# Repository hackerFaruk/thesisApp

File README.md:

# thesisApp

This app is made to work as part of my master thesis.
Controls motors & observes data of an exoskeleton.
Exoskeleton is also built as part of my master

Thesis name:
#  Development of Body Position and Muscle State Analyzing Personal Trainer Device with Mobile App Support

Thesis Ref no ( Turkey) : 10604256

my orcid 0000-0001-7512-0224

# Folder Structure 

control_app -> file you can find mobile app made with flutter  

Step Files ->  you can step files for either prodcution or editting  parts used in thesis   

Visuals -> you can find technical drawings of parts and also pictures of end product  

Embeded -> you can find files regarding embeded files   

Electronics -> you can find electronics for embeded system in here 

# Requirements  For  Flutter App 

Flutter SDK
Android Toolchain
Java Development Kit 

You can either visit flutter.dev for setup your development environment ( https://docs.flutter.dev/get-started/install )

or 

1- manually install flutter sdk   

2- run command <flutter doctor>  to check if any requirements are missing 

3- Get Java development kit ( JDK) from oracle

4- to get android tool chain use  Android Studio > Tools > SDK tools > Android SDK Command-line Tools >Apply to get sdk 

5- run <flutter doctor --android-licenses>  this step might require 

Recomended : Use Android Stuido to setup and device emulator (  this is not a requiremnt for this to work but definetly useful for development or testing )

# Versions List 

sdk: '>=2.19.4 <3.0.0' 

cupertino_icons: ^1.0.2

flutter_bluetooth_serial: ^0.4.0

flutter_lints: ^2.0.0

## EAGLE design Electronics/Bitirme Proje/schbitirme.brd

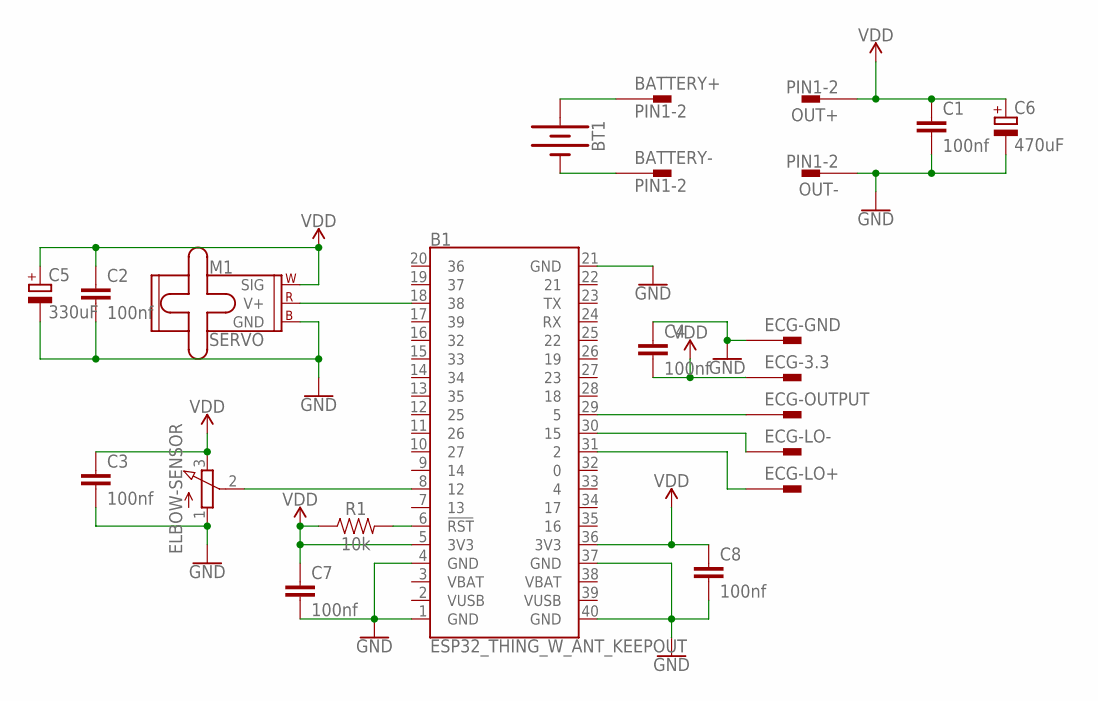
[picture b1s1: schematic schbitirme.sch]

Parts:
B1: ESP32_THING_W_ANT_KEEPOUT; ESP32_THING
BATTERY+: PIN1-2; 62221
BATTERY-: PIN1-2; 62221
BT1: BATTERY-18650; BATTERY_18650-HOLDER
C1, C2, C3, C4, C7, C8: 100nf; C2.5-3
C5: 330uF; PANASONIC_D
C6: 470uF; PANASONIC_D
ECG-3.3: PIN1-2; 62221
ECG-GND: PIN1-2; 62221
ECG-LO+: PIN1-2; 62221
ECG-LO-: PIN1-2; 62221
ECG-OUTPUT: PIN1-2; 62221
ELBOW-SENSOR: 3RP/1610N
M1: SERVO; 1X03
OUT+: PIN1-2; 62221
OUT-: PIN1-2; 62221
R1: 10k; 0603

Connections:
GND: B1.1 (GND), B1.4 (GND), B1.21 (GND), B1.37 (GND), B1.40 (GND), C1.2, C2.2, C3.2, C4.1, C5.-, C6.-, C7.2, C8.2, ECG-GND.1, ELBOW-SENSOR.1 (A), M1.3 (GND), OUT-.1
unnamed: BATTERY+.1, BT1.PWR@1 (+)
unnamed: BATTERY-.1, BT1.GND@1 (-)
unnamed: B1.18 (38), M1.2 (V+)
unnamed: B1.8 (12), ELBOW-SENSOR.2 (S)
unnamed: B1.29 (5), ECG-OUTPUT.1
unnamed: B1.30 (15), ECG-LO-.1
unnamed: B1.31 (2), ECG-LO+.1
unnamed: B1.6 (!RST!), R1.2
VDD: B1.5 (3V3), B1.36 (3V3), C1.1, C2.1, C3.1, C4.2, C5.+, C6.+, C7.1, C8.1, ECG-3.3.1, ELBOW-SENSOR.3 (E), M1.1 (SIG), OUT+.1, R1.1

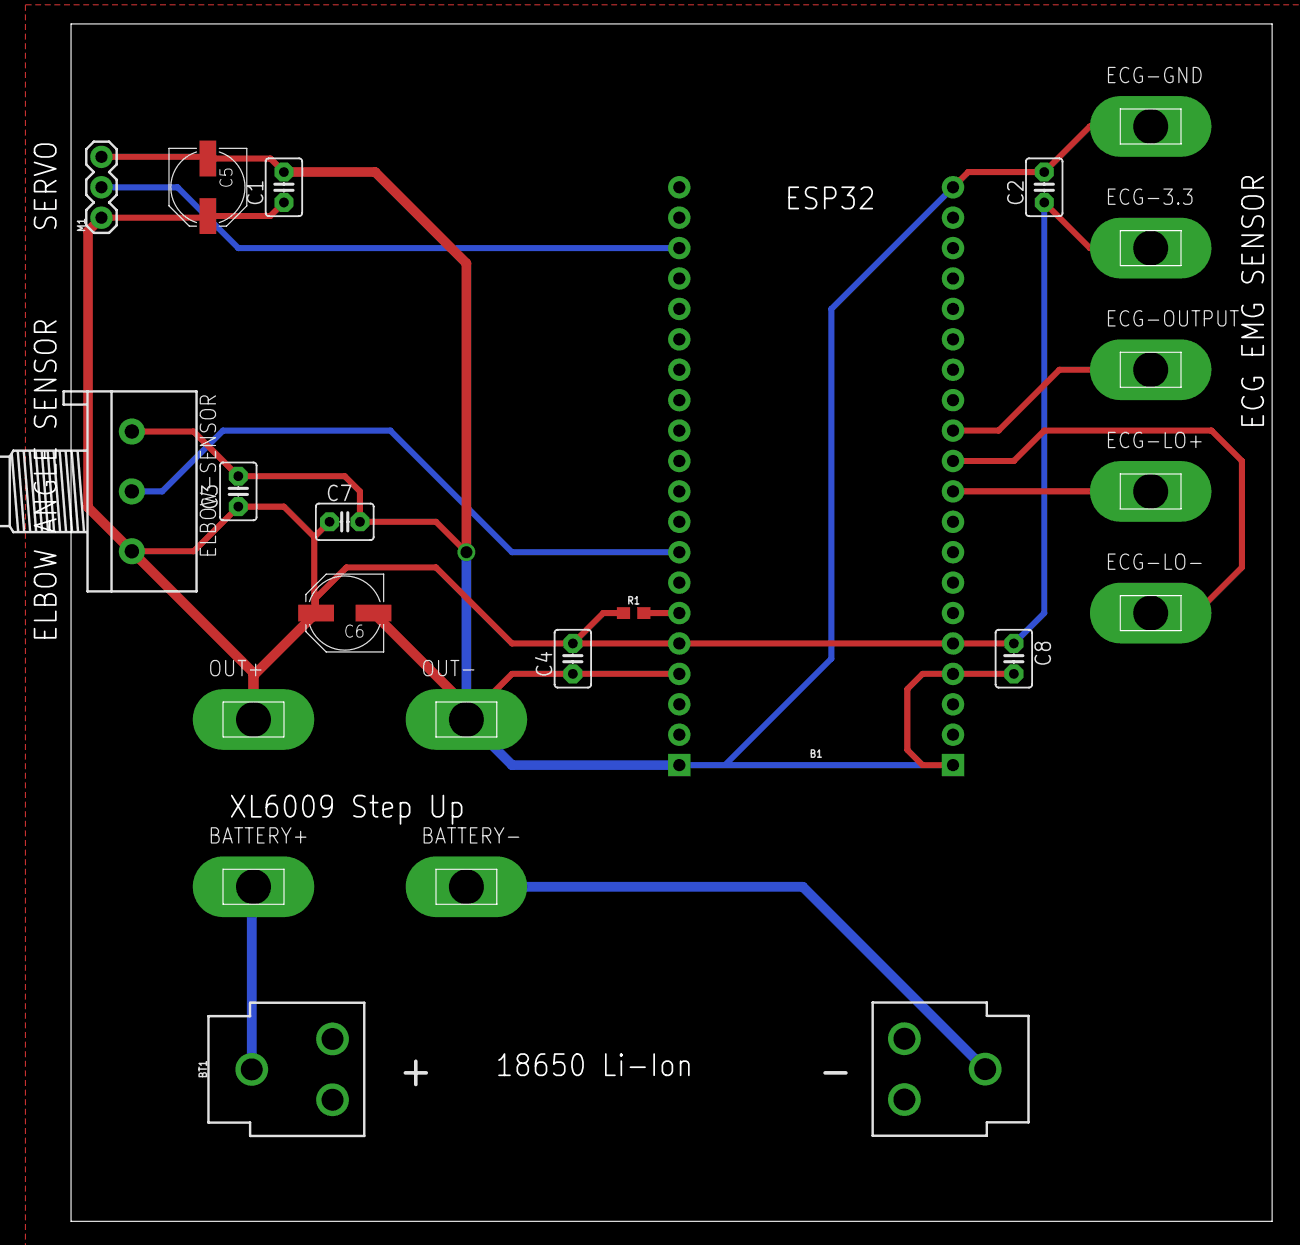
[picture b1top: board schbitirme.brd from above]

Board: 2 copper layers, 104.6 x 100.0 mm, 22 parts (0 on the bottom side), 10 nets.

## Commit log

2023-03-11 basic coloring
2023-03-11 centered picture
2023-03-11 icons and other
2023-03-12 added buttons
2023-03-12 buttons
2023-03-12 added secon button
2023-03-12 needs to be resposnive
2023-03-12 added state
2023-03-12 corretccted tooltip
2023-03-12 used with parameters
2023-03-12 gesture detector
2023-03-12 added some gesture mechanics
2023-03-12 hala widgtere onpressed ekleyemedim
2023-03-12 random çalişiyor gesture detector
2023-03-13 responsive screen
2023-03-13 constrains added
2023-03-13 added blutooh page
2023-03-13 size color
2023-03-13 comma
2023-03-13 fixed merge
2023-03-13 added buutton sizes
2023-03-13 page changes are made
2023-03-13 better button
2023-03-20 imported blutooh
2023-04-06 general look and feel enchantments
2023-04-07 faruk
2023-11-17 bir sürü değişikllik
2023-11-17 added const values
2023-11-17 new pages and apps
2023-12-29 newfiles

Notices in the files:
parts and their libraries:
SparkFun-Boards: Licensing: Creative Commons ShareAlike 4.0 International - https://creativecommons.org/licenses/by-sa/4.0
